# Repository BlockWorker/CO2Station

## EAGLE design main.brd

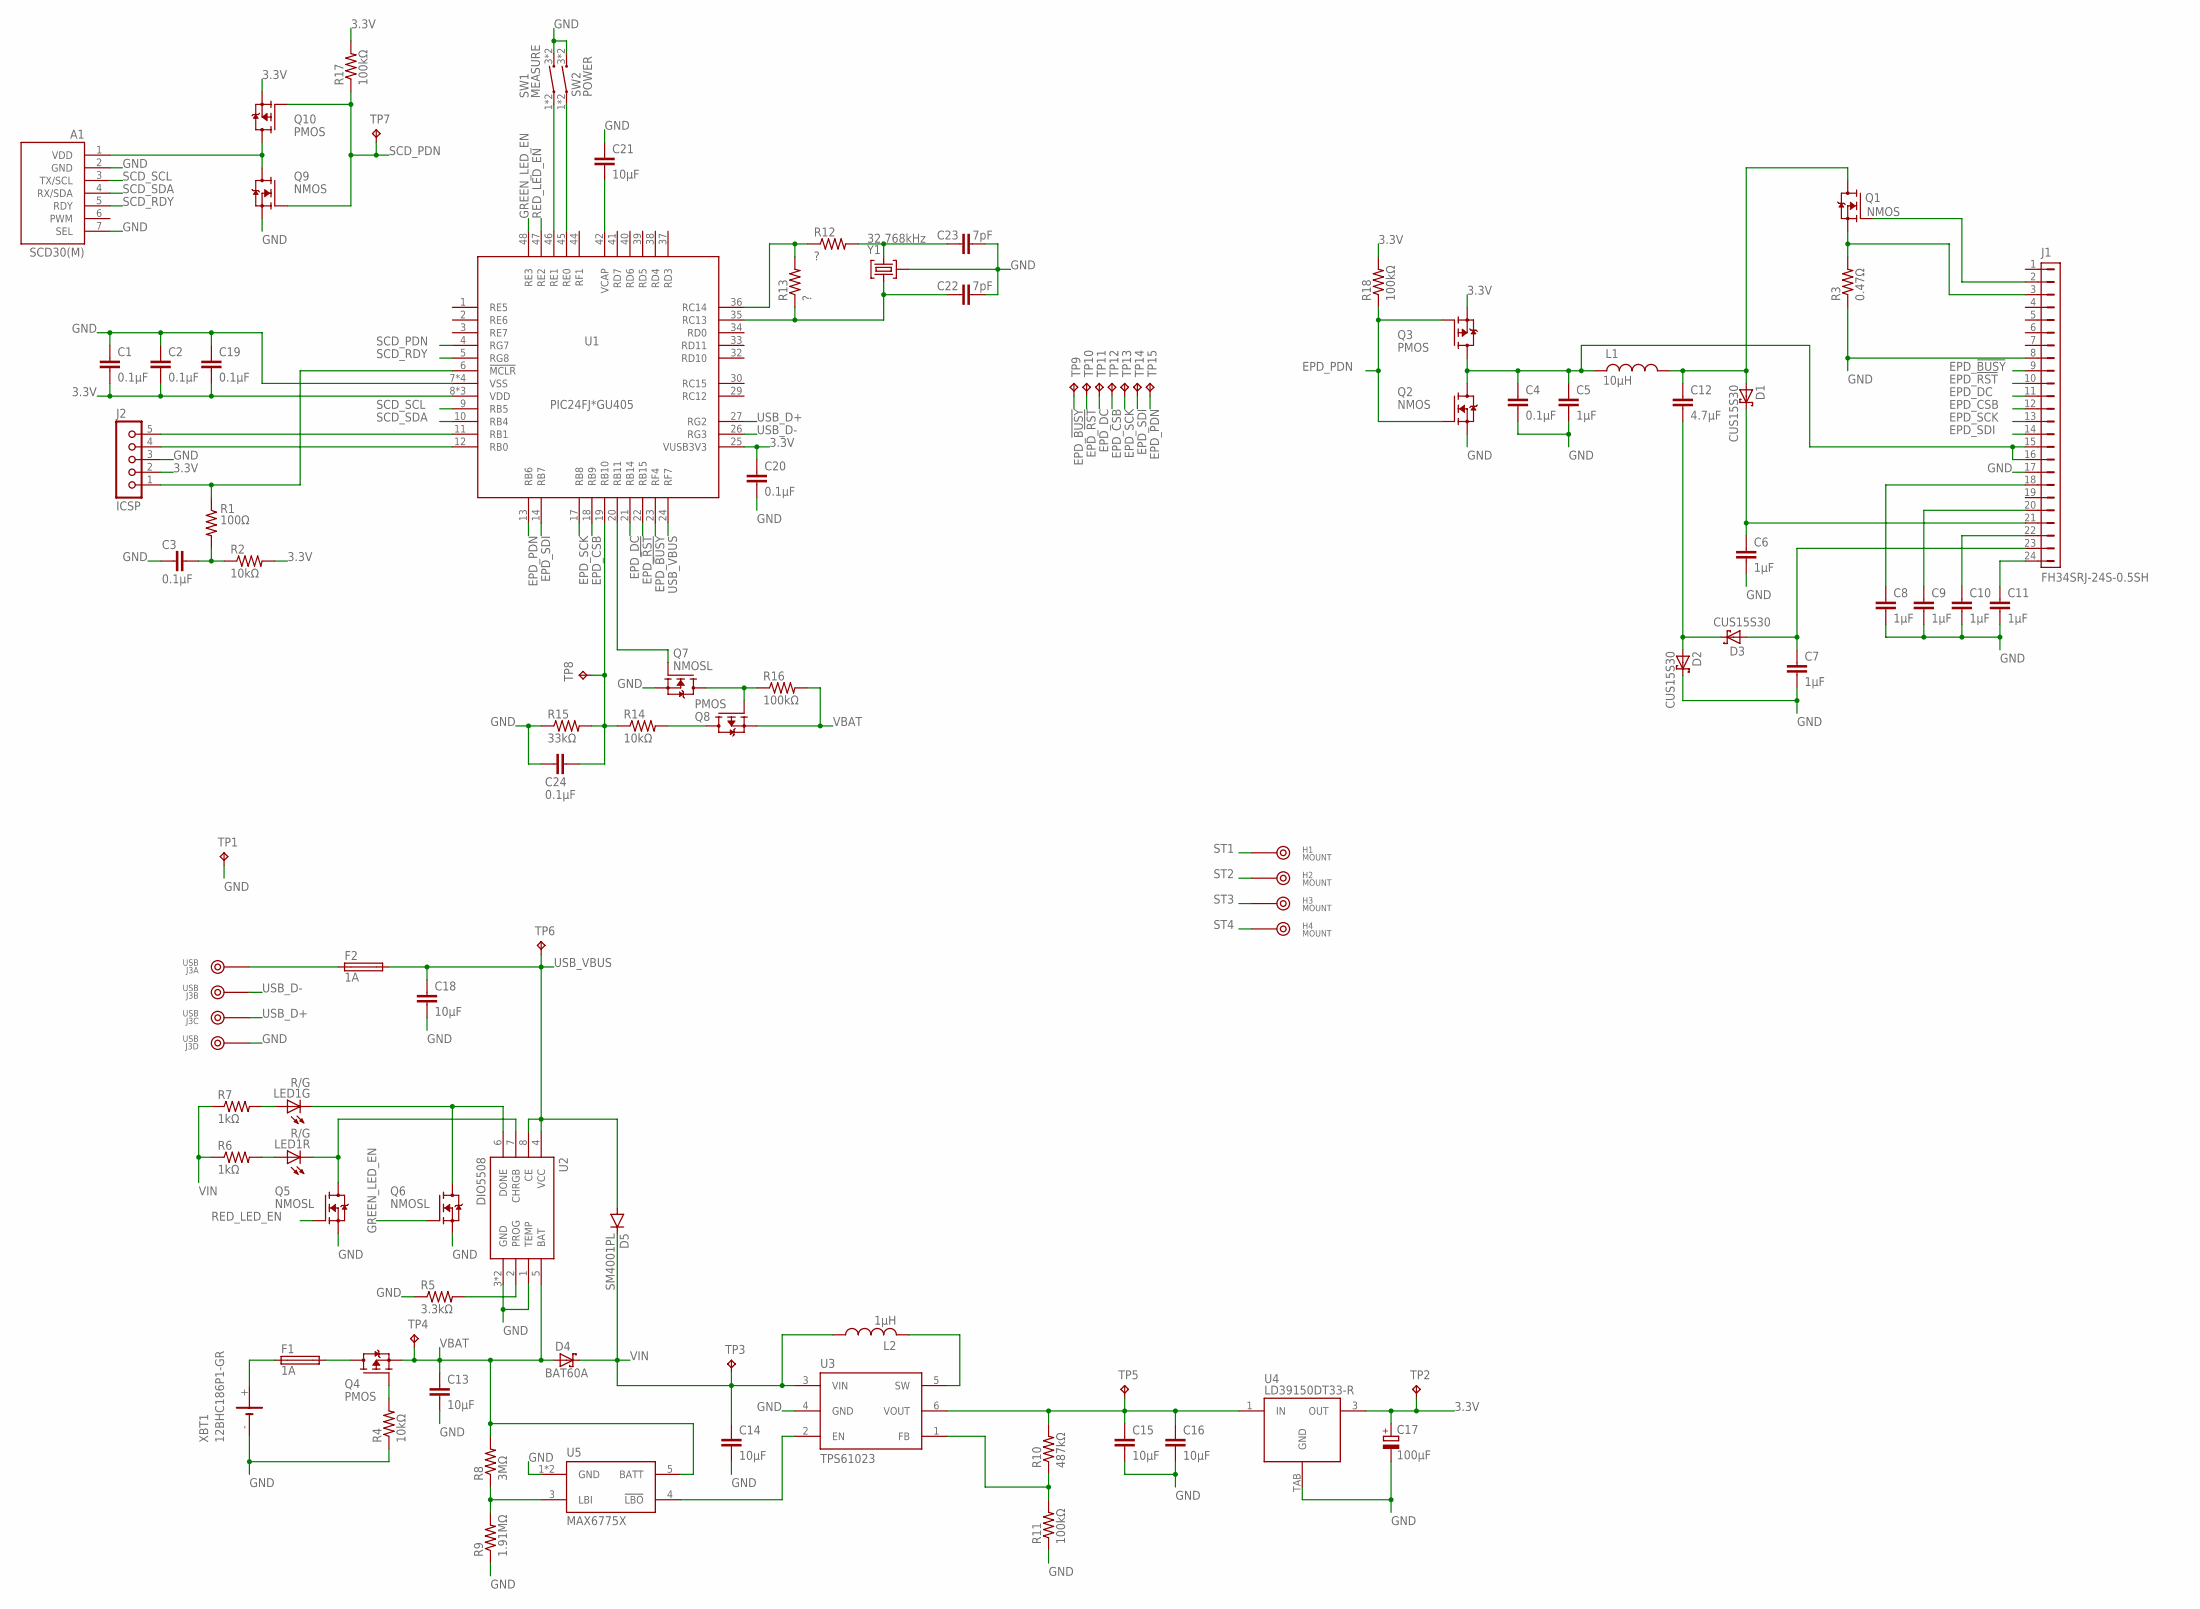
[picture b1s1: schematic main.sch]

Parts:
A1: SCD30(M); SCD30-MIRRORED
C1, C2, C3, C4, C19, C20, C24: 0.1µF; C0603
C5, C6, C7, C8, C9, C10, C11: 1µF; C0603
C12: 4.7µF; C0805
C13, C14, C15, C16, C18, C21: 10µF; C0805
C17: 100µF; PANASONIC_D
C22, C23: 7pF; C0603
D1, D2, D3: CUS15S30; SOD323
D4: BAT60A; SOD323
D5: SM4001PL; SOD123
F1, F2: 1A; C0603
H1, H2, H3, H4: MOUNT; 7466313R
J1: FH34SRJ-24S-0.5SH
J2: ICSP; 5PIN-1.27
J3: USB; 4PIN
L1: 10µH; L3225M
L2: 1µH; TYS4030
LED1: R/G; 0805-DUALLED
Q1, Q2, Q9: NMOS; SOT23
Q3, Q4, Q8, Q10: PMOS; SOT23
Q5, Q6, Q7: NMOSL; SOT23
R1: 100Ω; R0603
R2, R4, R14: 10kΩ; R0603
R3: 0.47Ω; R0603
R5: 3.3kΩ; R0603
R6, R7: 1kΩ; R0603
R8: 3MΩ; R0603
R9: 1.91MΩ; R0603
R10: 487kΩ; R0603
R11, R16, R17, R18: 100kΩ; R0603
R12, R13: ?; R0603
R15: 33kΩ; R0603
SW1: MEASURE; PTS647
SW2: POWER; PTS647
TP1, TP2, TP3, TP4, TP5, TP6, TP7, TP8, TP9, TP10, TP11, TP12, TP13, TP14, TP15: RCU-0(J); TP_0603_JOINED
U1: PIC24FJ*GU405; TQFP48
U2: DIO5508; SOIC8-EP
U3: TPS61023; SOT563
U4: LD39150DT33-R; DPAK
U5: MAX6775X; SC70-5
XBT1: 12BHC186P1-GR
Y1: 32.768kHz; MS1V-T1K

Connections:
3.3V: C1.2, C2.2, C17.+, C19.2, C20.1, J2.2, Q3.2 (S), Q10.2 (S), R2.2, R17.2, R18.2, TP2.1, U1.8 (VDD), U1.15 (VDD), U1.25 (VUSB3V3), U1.28 (VDD), U4.3 (OUT)
!MCLR: J2.1, R1.1, U1.6 (!MCLR)
!MCLR!_FILTER: C3.1, R1.2, R2.1
BAT_!LBO: U3.2 (EN), U5.4 (!LBO)
BAT_LBI: R8.1, R9.2, U5.3 (LBI)
BAT_RPP_GATE: Q4.1 (G), R4.2
BOOST_FB: R10.1, R11.2, U3.1 (FB)
BOOST_SW: L2.2, U3.5 (SW)
BOOST_VOUT: C15.1, C16.1, R10.2, TP5.1, U3.6 (VOUT), U4.1 (IN)
CHG_LED_G: LED1.K2 (C), Q6.3 (D), U2.6 (DONE)
CHG_LED_G_RES: LED1.A2 (A), R7.2
CHG_LED_R: LED1.K1 (C), Q5.3 (D), U2.7 (CHRGB)
CHG_LED_R_RES: LED1.A1 (A), R6.2
CHG_PROG: R5.2, U2.2 (PROG)
EPD_!BUSY: J1.9, TP9.1, U1.23 (RF4)
EPD_!RST: J1.10, TP10.1, U1.22 (RB15)
EPD_BOOST: C12.1, D1.2 (A), L1.2, Q1.3 (D)
EPD_BOOST_LOW: C12.2, D2.2 (A), D3.1 (C)
EPD_CS: J1.3, Q1.2 (S), R3.2
EPD_CSB: J1.12, TP12.1, U1.18 (RB9)
EPD_DC: J1.11, TP11.1, U1.21 (RB14)
EPD_GDR: J1.2, Q1.1 (G)
EPD_PDN: Q2.1 (G), Q3.1 (G), R18.1, TP15.1, U1.13 (RB6)
EPD_SCK: J1.13, TP13.1, U1.17 (RB8)
EPD_SDI: J1.14, TP14.1, U1.14 (RB7)
EPD_VCOM: C11.1, J1.24
EPD_VDD: C4.1, C5.1, J1.15, J1.16, L1.1, Q2.3 (D), Q3.3 (D)
EPD_VDDD: C8.1, J1.18
EPD_VDH: C9.1, J1.20
EPD_VDL: C10.1, J1.22
EPD_VGH: C6.1, D1.1 (C), J1.21
EPD_VGL: C7.1, D3.2 (A), J1.23
GND: A1.2 (GND), A1.7 (SEL), C1.1, C2.1, C3.2, C4.2, C5.2, C6.2, C7.2, C8.2, C9.2, C10.2, C11.2, C13.2, C14.2, C15.2, C16.2, C17.-, C18.2, C19.1, C20.2, C21.1, C22.2, C23.2, C24.2, D2.1 (C), J1.8, J1.17, J2.3, J3.4, Q2.2 (S), Q5.2 (S), Q6.2 (S), Q7.2 (S), Q9.2 (S), R3.1, R4.1, R5.1, R9.1, R11.1, R15.1, SW1.3 (2), SW1.4 (2), SW2.3 (2), SW2.4 (2), TP1.1, U1.7 (VSS), U1.16 (VSS), U1.31 (VSS), U1.43 (VSS), U2.1 (TEMP), U2.3 (GND), U2.EP (GND), U3.4 (GND), U4.TAB (GND), U5.1 (GND), U5.2 (GND), XBT1.-, Y1.GND (3)
GREEN_LED_EN: Q6.1 (G), U1.48 (RE3)
ICSPCLK: J2.5, U1.11 (RB1)
ICSPDAT: J2.4, U1.12 (RB0)
MCU_MEASURESW: SW1.1, SW1.2 (1), U1.46 (RE1)
MCU_POWERSW: SW2.1, SW2.2 (1), U1.45 (RE0)
MCU_SOSCI: C22.1, R13.1, U1.35 (RC13), Y1.2
MCU_SOSCO: R12.1, R13.2, U1.36 (RC14)
MCU_SOSCO_R: C23.1, R12.2, Y1.1
MCU_VCAP: C21.2, U1.42 (VCAP)
RED_LED_EN: Q5.1 (G), U1.47 (RE2)
SCD_PDN: Q9.1 (G), Q10.1 (G), R17.1, TP7.1, U1.4 (RG7)
SCD_RDY: A1.5 (RDY), U1.5 (RG8)
SCD_SCL: A1.3 (TX/SCL), U1.9 (RB5)
SCD_SDA: A1.4 (RX/SDA), U1.10 (RB4)
SCD_VDD: A1.1 (VDD), Q9.3 (D), Q10.3 (D)
ST1: H1.H1, H1.H2, H1.P
ST2: H2.H1, H2.H2, H2.P
ST3: H3.H1, H3.H2, H3.P
ST4: H4.H1, H4.H2, H4.P
USB_D+: J3.3, U1.27 (RG2)
USB_D-: J3.2, U1.26 (RG3)
USB_VBUS: C18.1, D5.A, F2.2, TP6.1, U1.24 (RF7), U2.4 (VCC), U2.8 (CE)
USB_VBUS_RAW: F2.1, J3.1
VBAT: C13.1, D4.2 (A), Q4.2 (S), Q8.2 (S), R8.2, R16.2, TP4.1, U2.5 (BAT), U5.5 (BATT)
VBAT_FUSED: F1.2, Q4.3 (D)
VBAT_GATECTL: Q7.3 (D), Q8.1 (G), R16.1
VBAT_GATED: Q8.3 (D), R14.2
VBAT_MEASURE: C24.1, R14.1, R15.2, TP8.1, U1.19 (RB10)
VBAT_MEASURE_EN: Q7.1 (G), U1.20 (RB11)
VBAT_RAW: F1.1, XBT1.+
VIN: C14.1, D4.1 (C), D5.C, L2.1, R6.1, R7.1, TP3.1, U3.3 (VIN)

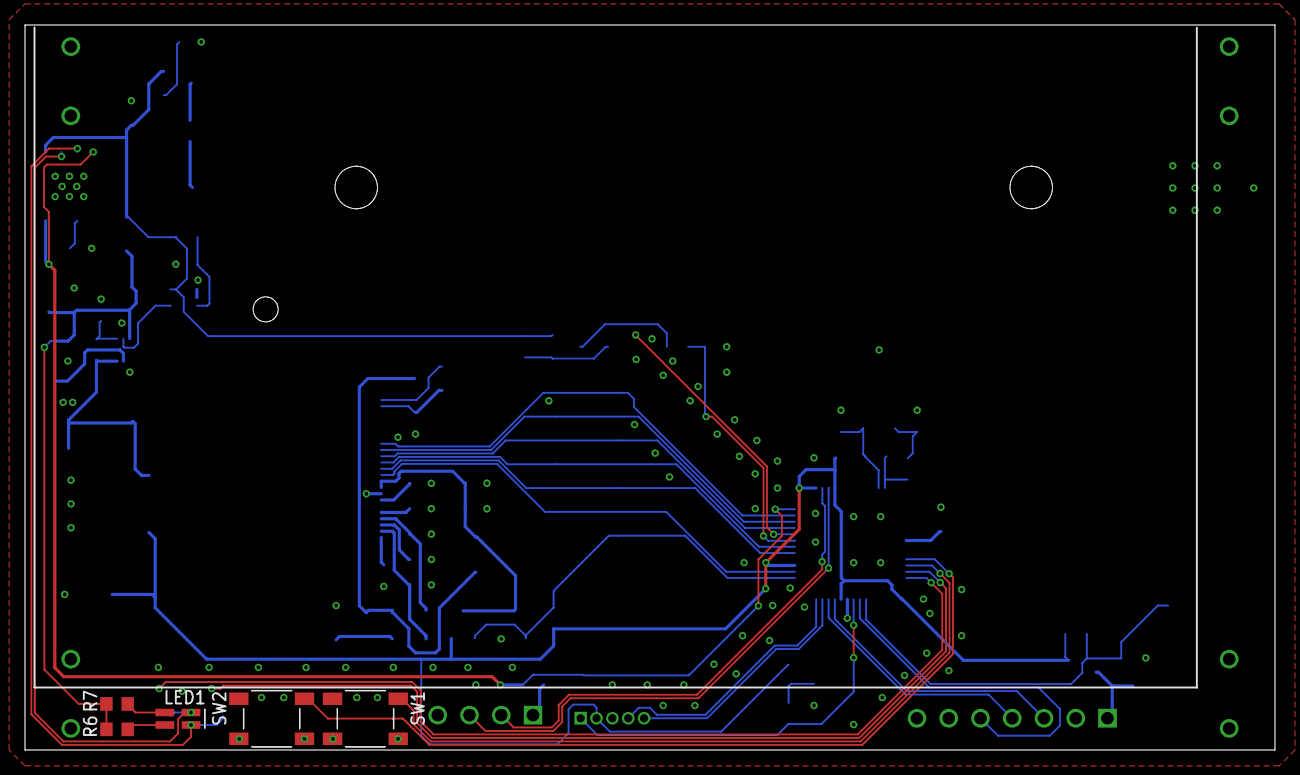
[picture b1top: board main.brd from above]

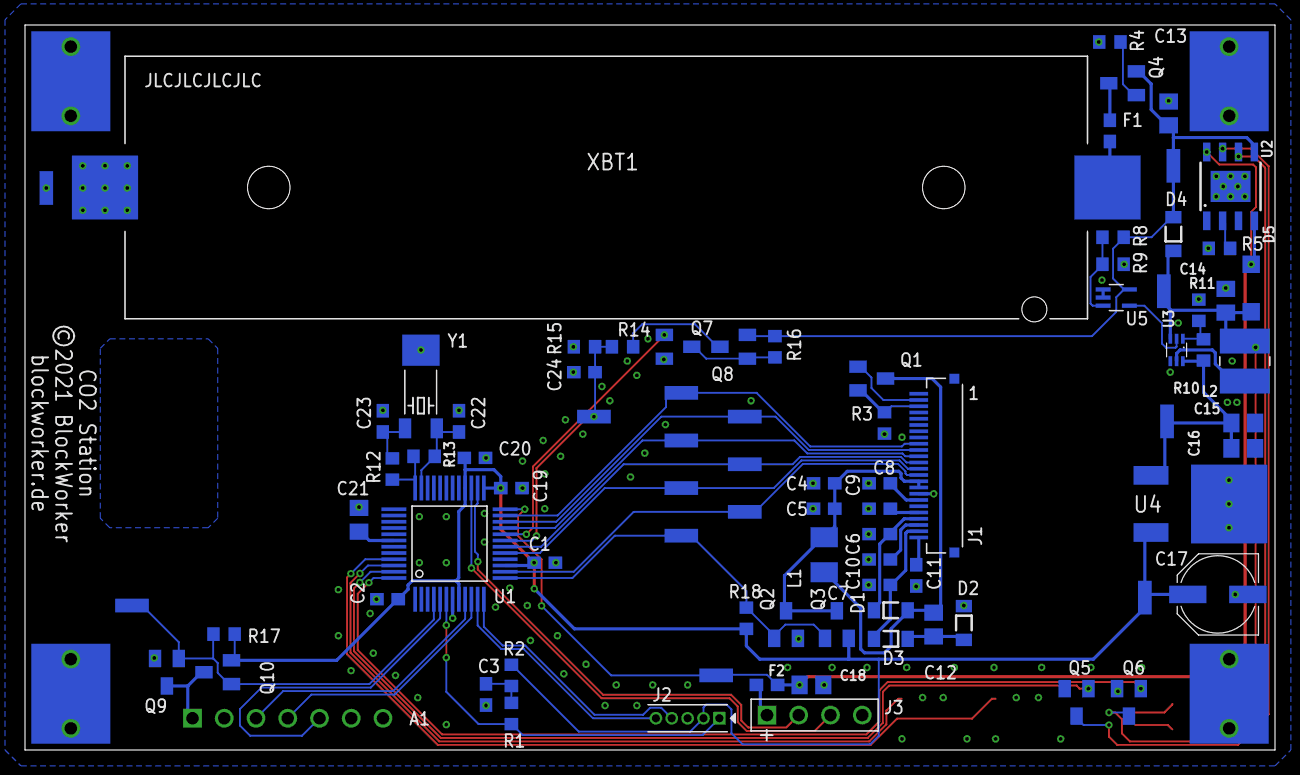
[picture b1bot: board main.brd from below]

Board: 2 copper layers, 100.0 x 58.0 mm, 94 parts (89 on the bottom side), 64 nets.

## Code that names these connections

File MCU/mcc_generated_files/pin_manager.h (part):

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*/
/**
  @Summary
    Sets the GPIO pin, RB10, high using LATB10.

  @Description
    Sets the GPIO pin, RB10, high using LATB10.

  @Preconditions
    The RB10 must be set to an output.
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#define BAT_SENSE_SetHigh()          (_LATB10 = 1)
/**
  @Summary
    Sets the GPIO pin, RB10, low using LATB10.

  @Description
    Sets the GPIO pin, RB10, low using LATB10.

  @Preconditions
    The RB10 must be set to an output.
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#define BAT_SENSE_SetLow()           (_LATB10 = 0)
/**
  @Summary
    Toggles the GPIO pin, RB10, using LATB10.

  @Description
    Toggles the GPIO pin, RB10, using LATB10.

  @Preconditions
    The RB10 must be set to an output.
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#define BAT_SENSE_Toggle()           (_LATB10 ^= 1)
/**
  @Summary
    Reads the value of the GPIO pin, RB10.

  @Description
    Reads the value of the GPIO pin, RB10.

  @Preconditions
    None.
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    </code>

*/
#define BAT_SENSE_GetValue()         _RB10
/**
  @Summary
    Configures the GPIO pin, RB10, as an input.

  @Description
    Configures the GPIO pin, RB10, as an input.

  @Preconditions
    None.
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#define BAT_SENSE_SetDigitalInput()  (_TRISB10 = 1)
/**
  @Summary
    Configures the GPIO pin, RB10, as an output.

  @Description
    Configures the GPIO pin, RB10, as an output.

  @Preconditions
    None.
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#define BAT_SENSE_SetDigitalOutput() (_TRISB10 = 0)
/**
  @Summary
    Sets the GPIO pin, RB11, high using LATB11.

  @Description
    Sets the GPIO pin, RB11, high using LATB11.

  @Preconditions
    The RB11 must be set to an output.
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#define BAT_SENSE_EN_SetHigh()          (_LATB11 = 1)
/**
  @Summary
    Sets the GPIO pin, RB11, low using LATB11.

  @Description
    Sets the GPIO pin, RB11, low using LATB11.

  @Preconditions
    The RB11 must be set to an output.
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#define BAT_SENSE_EN_SetLow()           (_LATB11 = 0)
/**
  @Summary
    Toggles the GPIO pin, RB11, using LATB11.

  @Description
    Toggles the GPIO pin, RB11, using LATB11.

  @Preconditions
    The RB11 must be set to an output.
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#define BAT_SENSE_EN_Toggle()           (_LATB11 ^= 1)
/**
  @Summary
    Reads the value of the GPIO pin, RB11.

  @Description
    Reads the value of the GPIO pin, RB11.

  @Preconditions
    None.
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    </code>

*/
#define BAT_SENSE_EN_GetValue()         _RB11
/**
  @Summary
    Configures the GPIO pin, RB11, as an input.

  @Description
    Configures the GPIO pin, RB11, as an input.

  @Preconditions
    None.
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#define BAT_SENSE_EN_SetDigitalInput()  (_TRISB11 = 1)
/**
  @Summary
    Configures the GPIO pin, RB11, as an output.

  @Description
    Configures the GPIO pin, RB11, as an output.

  @Preconditions
    None.
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#define BAT_SENSE_EN_SetDigitalOutput() (_TRISB11 = 0)
/**
  @Summary
    Sets the GPIO pin, RB14, high using LATB14.

  @Description
    Sets the GPIO pin, RB14, high using LATB14.

  @Preconditions
    The RB14 must be set to an output.
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#define EPD_DC_SetHigh()          (_LATB14 = 1)
/**
  @Summary
    Sets the GPIO pin, RB14, low using LATB14.

  @Description
    Sets the GPIO pin, RB14, low using LATB14.

  @Preconditions
    The RB14 must be set to an output.
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#define EPD_DC_SetLow()           (_LATB14 = 0)
/**
  @Summary
    Toggles the GPIO pin, RB14, using LATB14.

  @Description
    Toggles the GPIO pin, RB14, using LATB14.

  @Preconditions
    The RB14 must be set to an output.
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#define EPD_DC_Toggle()           (_LATB14 ^= 1)
/**
  @Summary
    Reads the value of the GPIO pin, RB14.

  @Description
    Reads the value of the GPIO pin, RB14.

  @Preconditions
    None.
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    </code>

*/
#define EPD_DC_GetValue()         _RB14
/**
  @Summary
    Configures the GPIO pin, RB14, as an input.

  @Description
    Configures the GPIO pin, RB14, as an input.

  @Preconditions
    None.
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#define EPD_DC_SetDigitalInput()  (_TRISB14 = 1)
/**
  @Summary
    Configures the GPIO pin, RB14, as an output.

  @Description
    Configures the GPIO pin, RB14, as an output.

  @Preconditions
    None.
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#define EPD_DC_SetDigitalOutput() (_TRISB14 = 0)
/**
  @Summary
    Sets the GPIO pin, RB15, high using LATB15.

  @Description
    Sets the GPIO pin, RB15, high using LATB15.

  @Preconditions
    The RB15 must be set to an output.
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#define EPD_RST_N_SetHigh()          (_LATB15 = 1)
/**
  @Summary
    Sets the GPIO pin, RB15, low using LATB15.

  @Description
    Sets the GPIO pin, RB15, low using LATB15.

  @Preconditions
    The RB15 must be set to an output.
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#define EPD_RST_N_SetLow()           (_LATB15 = 0)
/**
  @Summary
    Toggles the GPIO pin, RB15, using LATB15.

  @Description
    Toggles the GPIO pin, RB15, using LATB15.

  @Preconditions
    The RB15 must be set to an output.
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#define EPD_RST_N_Toggle()           (_LATB15 ^= 1)
/**
  @Summary
    Reads the value of the GPIO pin, RB15.

  @Description
    Reads the value of the GPIO pin, RB15.

  @Preconditions
    None.
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    </code>

*/
#define EPD_RST_N_GetValue()         _RB15
/**
  @Summary
    Configures the GPIO pin, RB15, as an input.

  @Description
    Configures the GPIO pin, RB15, as an input.

  @Preconditions
    None.
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#define EPD_RST_N_SetDigitalInput()  (_TRISB15 = 1)
/**
  @Summary
    Configures the GPIO pin, RB15, as an output.

  @Description
    Configures the GPIO pin, RB15, as an output.

  @Preconditions
    None.
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#define EPD_RST_N_SetDigitalOutput() (_TRISB15 = 0)
/**
  @Summary
    Sets the GPIO pin, RB6, high using LATB6.

  @Description
    Sets the GPIO pin, RB6, high using LATB6.

  @Preconditions
    The RB6 must be set to an output.
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#define EPD_PDN_SetHigh()          (_LATB6 = 1)
/**
  @Summary
    Sets the GPIO pin, RB6, low using LATB6.

  @Description
    Sets the GPIO pin, RB6, low using LATB6.

  @Preconditions
    The RB6 must be set to an output.
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#define EPD_PDN_SetLow()           (_LATB6 = 0)
/**
  @Summary
    Toggles the GPIO pin, RB6, using LATB6.

  @Description
    Toggles the GPIO pin, RB6, using LATB6.

  @Preconditions
    The RB6 must be set to an output.
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#define EPD_PDN_Toggle()           (_LATB6 ^= 1)
/**
  @Summary
    Reads the value of the GPIO pin, RB6.

  @Description
    Reads the value of the GPIO pin, RB6.

  @Preconditions
    None.
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    </code>

*/
#define EPD_PDN_GetValue()         _RB6
/**
  @Summary
    Configures the GPIO pin, RB6, as an input.

  @Description
    Configures the GPIO pin, RB6, as an input.

  @Preconditions
    None.
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#define EPD_PDN_SetDigitalInput()  (_TRISB6 = 1)
/**
  @Summary
    Configures the GPIO pin, RB6, as an output.

  @Description
    Configures the GPIO pin, RB6, as an output.

  @Preconditions
    None.
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#define EPD_PDN_SetDigitalOutput() (_TRISB6 = 0)
/**
  @Summary
    Sets the GPIO pin, RB7, high using LATB7.

  @Description
    Sets the GPIO pin, RB7, high using LATB7.

  @Preconditions
    The RB7 must be set to an output.
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#define SDO1_SetHigh()          (_LATB7 = 1)
/**
  @Summary
    Sets the GPIO pin, RB7, low using LATB7.

  @Description
    Sets the GPIO pin, RB7, low using LATB7.

  @Preconditions
    The RB7 must be set to an output.
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#define SDO1_SetLow()           (_LATB7 = 0)
/**
  @Summary
    Toggles the GPIO pin, RB7, using LATB7.

  @Description
    Toggles the GPIO pin, RB7, using LATB7.

  @Preconditions
    The RB7 must be set to an output.
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#define SDO1_Toggle()           (_LATB7 ^= 1)
/**
  @Summary
    Reads the value of the GPIO pin, RB7.

  @Description
    Reads the value of the GPIO pin, RB7.

  @Preconditions
    None.
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    </code>

*/
#define SDO1_GetValue()         _RB7
/**
  @Summary
    Configures the GPIO pin, RB7, as an input.

  @Description
    Configures the GPIO pin, RB7, as an input.

  @Preconditions
    None.
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#define SDO1_SetDigitalInput()  (_TRISB7 = 1)
/**
  @Summary
    Configures the GPIO pin, RB7, as an output.

  @Description
    Configures the GPIO pin, RB7, as an output.

  @Preconditions
    None.
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#define SDO1_SetDigitalOutput() (_TRISB7 = 0)
/**
  @Summary
    Sets the GPIO pin, RB8, high using LATB8.

  @Description
    Sets the GPIO pin, RB8, high using LATB8.

  @Preconditions
    The RB8 must be set to an output.
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#define SCK1_SetHigh()          (_LATB8 = 1)
/**
  @Summary
    Sets the GPIO pin, RB8, low using LATB8.

  @Description
    Sets the GPIO pin, RB8, low using LATB8.

  @Preconditions
    The RB8 must be set to an output.
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#define SCK1_SetLow()           (_LATB8 = 0)
/**
  @Summary
    Toggles the GPIO pin, RB8, using LATB8.

  @Description
    Toggles the GPIO pin, RB8, using LATB8.

  @Preconditions
    The RB8 must be set to an output.
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#define SCK1_Toggle()           (_LATB8 ^= 1)
/**
  @Summary
    Reads the value of the GPIO pin, RB8.

  @Description
    Reads the value of the GPIO pin, RB8.

  @Preconditions
    None.
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    </code>

*/
#define SCK1_GetValue()         _RB8
/**
  @Summary
    Configures the GPIO pin, RB8, as an input.

  @Description
    Configures the GPIO pin, RB8, as an input.

  @Preconditions
    None.
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#define SCK1_SetDigitalInput()  (_TRISB8 = 1)
/**
  @Summary
    Configures the GPIO pin, RB8, as an output.

  @Description
    Configures the GPIO pin, RB8, as an output.
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
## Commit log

2021-10-19 Initial commit - PCB placement done
2021-10-20 Production version
2021-11-11 Code rework, SCD and EPD basic functionality
2021-11-30 Finalized version

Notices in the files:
MCU/mcc_generated_files/pin_manager.h:
(c) 2020 Microchip Technology Inc. and its subsidiaries. You may use this
main.brd:
©2021 BlockWorker
